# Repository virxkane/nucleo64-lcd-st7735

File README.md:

# nucleo64-lcd-st7735
LCD shield for STM32 Nucleo-64 boards.

This shield is designed for connecting to STM32 Nucleo-64 boards via Arduino<sup>TM</sup> Uno V3.

**WARNING:** Although this shield can be connected to the Arduino<sup>TM</sup> UNO, it is incompatible in logic levels, so it is strictly forbidden to connect this way, otherwise this display will fail!

### Hardware
* The GMT177-01 module is used as a display and is compatible in size and pins. The display controller used is **ST7735**. The display data bus is connected to the hardware SPI. PWM can be used  to control the brightness of the screen backlight.
* Joystick K1-1504SA-03 and one button KLS7-TS6601 can be used for control. Both are connected to 3 General Purpose I/O ports via diodes.
* EEPROM memory M24C08 can be used to store user data. This IC is connected to the I2C hardware bus.
* Two LEDs are connected to ports A0(PA0) and A1(PA1).
* A separate button IT-1187-160GM-G is provided to reset the controller.

### Demo firmware
Two versions of the demo firmware have been written to work on the NUCLEO-F446RE and this shield, one using CMSIS, the other using HAL. Both are under BSD-3-Clause License.
* Using CMSIS: [nucleo-f446re-st7735spi-shield](https://github.com/virxkane/nucleo-f446re-st7735spi-shield)
* Using HAL: [nucleo-f446re-st7735spi-shield-hal](https://github.com/virxkane/nucleo-f446re-st7735spi-shield-hal)

#### Compare performance
| # |  bpp variant  | fill period, ms | transfer period, CMSIS, ms | transfer period, HAL, ms |
|---|---------------|--------|-----------|---------|
| 1 | fb=1, lcd=12  |     3  |      23   |    40   |
| 2 | fb=1, lcd=16  |     3  |      30   |    60   |
| 3 | fb=1, lcd=18  |     3  |      44   |    74   |
| 4 | fb=4, lcd=12  |     3  |      23   |    39   |
| 5 | fb=4, lcd=16  |     3  |      30   |    58   |
| 6 | fb=4, lcd=18  |     3  |      44   |    73   |
| 7 | fb=8, lcd=12  |     2  |      23   |    39   |
| 8 | fb=8, lcd=16  |     2  |      30   |    59   |
| 9 | fb=8, lcd=18  |     2  |      44   |    73   |
| 10 | fb=16, lcd=12 |    3  |      22   |    39   |
| 11 | fb=16, lcd=16 |    3  |      30   |    59   |
| 12 | fb=16, lcd=18 |    3  |      44   |    75   |
| 13 | fb=24, lcd=12 |    3  |      22   |    38   |
| 14 | fb=24, lcd=16 |    3  |      30   |    61   |
| 15 | fb=24, lcd=18 |    3  |      44   |    73   |

Where *fb* - frame buffer color depth, *lcd* - LCD module color depth, *fill period* - frame buffer fill period, *transfer period* - period of frame buffer transmission to LCD module.

Tests performed at SPI clock 11,25 Mbits/s.

### Schematic

### Some photo
Unfortunately, there are currently no rev.4 boards, and the existing rev.3 boards have a small error - the LEDs are connected to RX/D0(PA3) and TX/D1(PA2), which by default are connected to the USART of the on-board ST-LINK/V2-1 programmer. To correct this drawback, two wire are placed on the bottom of the board to ports A0(PA0) and A1(PA1). The boards of the rev.4 are free from this drawback.

#### Front view (rev.3)

#### Back view (rev.3)

#### Paired with NUCLEO-F446RE with running [demo](https://github.com/virxkane/nucleo-f446re-st7735spi-shield) (rev.3)

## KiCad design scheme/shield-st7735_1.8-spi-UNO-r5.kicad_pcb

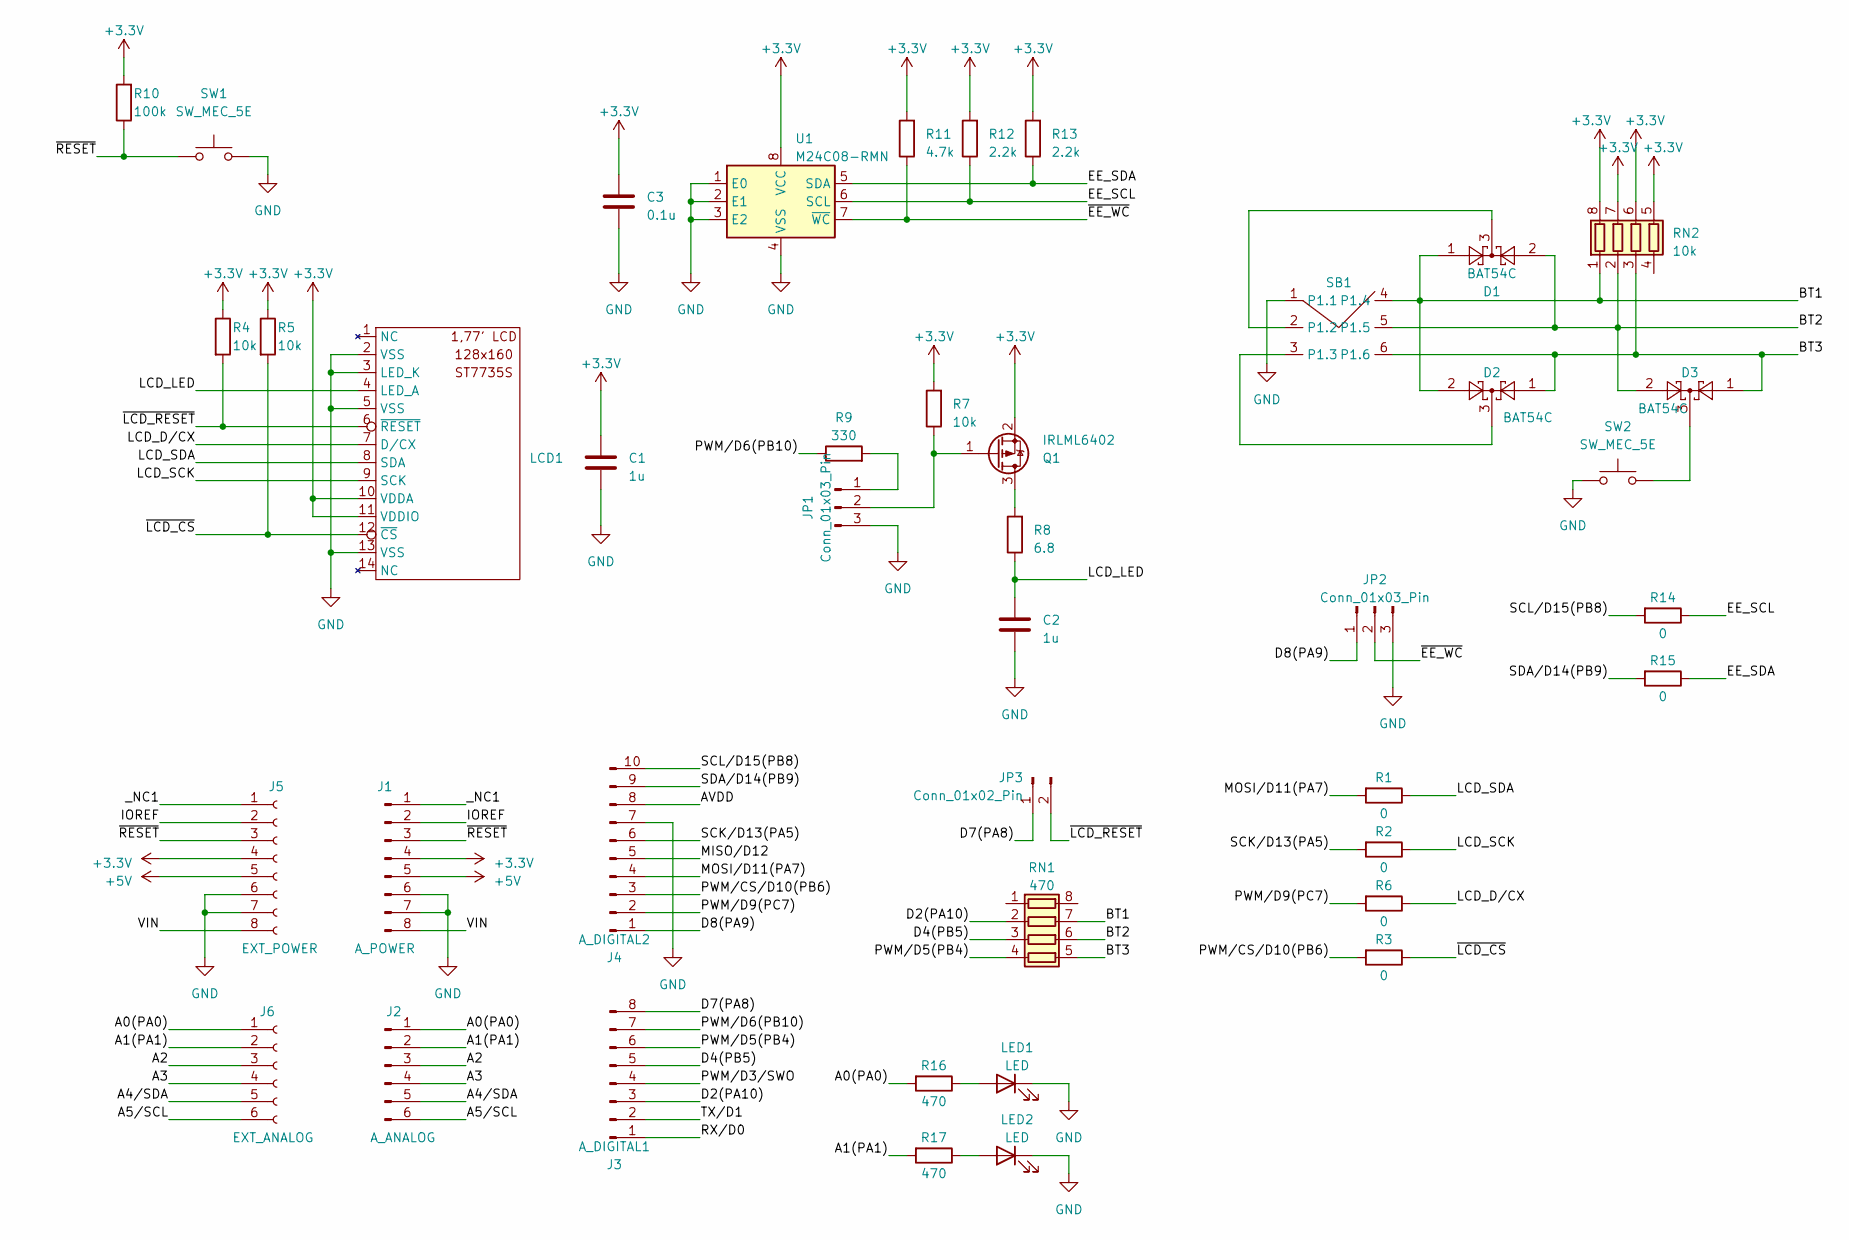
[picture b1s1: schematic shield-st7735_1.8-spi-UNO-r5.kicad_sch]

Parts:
C1, C2: 1u; C_1206_3216Metric
C3: 0.1u; C_1206_3216Metric
D1, D2, D3: BAT54C; SOT-23
J1: A_POWER; PinHeader_1x08_P2.54mm_Vertical
J2: A_ANALOG; PinHeader_1x06_P2.54mm_Vertical
J3: A_DIGITAL1; PinHeader_1x08_P2.54mm_Vertical
J4: A_DIGITAL2; PinHeader_1x10_P2.54mm_Vertical
J5: EXT_POWER; PinSocket_1x08_P2.54mm_Vertical
J6: EXT_ANALOG; PinSocket_1x06_P2.54mm_Vertical
JP1, JP2: Conn_01x03_Pin; PinHeader_1x03_P2.54mm_Vertical
JP3: Conn_01x02_Pin; PinHeader_1x02_P2.54mm_Vertical
LCD1: GMT177-01
LED1, LED2: LED; LED_0805_2012Metric
Q1: IRLML6402; SOT-23
R1, R2, R3, R6, R14, R15: 0; R_1206_3216Metric
R4, R5, R7: 10k; R_1206_3216Metric
R8: 6.8; R_1206_3216Metric
R9: 330; R_1206_3216Metric
R10: 100k; R_1206_3216Metric
R11: 4.7k; R_1206_3216Metric
R12, R13: 2.2k; R_1206_3216Metric
R16, R17: 470; R_1206_3216Metric
RN1: 470; R_Array_Convex_4x0603
RN2: 10k; R_Array_Convex_4x0603
SB1: K1-1504SA-03
SW1: SW_MEC_5E; SW_SPST_SKQG_WithStem
SW2: SW_MEC_5E; SW_PUSH_6mm_H4.3mm
U1: M24C08-RMN; SOIC-8_3.9x4.9mm_P1.27mm

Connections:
+3.3V: C1.1, C3.1, J1.4, J5.4, LCD1.10 (VDDA), LCD1.11 (VDDIO), Q1.2 (S), R4.1, R5.1, R7.2, R10.2, R11.2, R12.2, R13.2, RN2.5 (R4.2), RN2.6 (R3.2), RN2.7 (R2.2), RN2.8 (R1.2), U1.8 (VCC)
+5V: J1.5, J5.5
/A0(PA0): J2.1, J6.1, R16.2
/A1(PA1): J2.2, J6.2, R17.2
/A2: J2.3, J6.3
/A3: J2.4, J6.4
/A4/SDA: J2.5, J6.5
/A5/SCL: J2.6, J6.6
/AVDD: J4.8
/BT1: D1.1, D2.2, RN1.7 (R2.2), RN2.1 (R1.1), SB1.4 (P1.4)
/BT2: D1.2, D3.2, RN1.6 (R3.2), RN2.2 (R2.1), SB1.5 (P1.5)
/BT3: D2.1, D3.1, RN1.5 (R4.2), RN2.3 (R3.1), SB1.6 (P1.6)
/D2(PA10): J3.3, RN1.2 (R2.1)
/D4(PB5): J3.5, RN1.3 (R3.1)
/D7(PA8): J3.8, JP3.1
/D8(PA9): J4.1, JP2.1
/EE_SCL: R12.1, R14.1, U1.6 (SCL)
/EE_SDA: R13.1, R15.1, U1.5 (SDA)
/IOREF: J1.2, J5.2
/LCD_D/CX: LCD1.7 (D/CX), R6.1
/LCD_LED: C2.1, LCD1.4 (LED_A), R8.1
/LCD_SCK: LCD1.9 (SCK), R2.1
/LCD_SDA: LCD1.8 (SDA), R1.1
/MISO/D12: J4.5
/MOSI/D11(PA7): J4.4, R1.2
/PWM/CS/D10(PB6): J4.3, R3.2
/PWM/D3/SWO: J3.4
/PWM/D5(PB4): J3.6, RN1.4 (R4.1)
/PWM/D6(PB10): J3.7, R9.1
/PWM/D9(PC7): J4.2, R6.2
/RX/D0: J3.1
/SCK/D13(PA5): J4.6, R2.2
/SCL/D15(PB8): J4.10, R14.2
/SDA/D14(PB9): J4.9, R15.2
/TX/D1: J3.2
/VIN: J1.8, J5.8
/_NC1: J1.1, J5.1
/~EE_WC: JP2.2, R11.1, U1.7 (~WC)
/~LCD_CS: LCD1.12 (~CS), R3.1, R5.2
/~LCD_RESET: JP3.2, LCD1.6 (~RESET), R4.2
/~RESET: J1.3, J5.3, R10.1, SW1.1
GND: C1.2, C2.2, C3.2, J1.6, J1.7, J4.7, J5.6, J5.7, JP1.3, JP2.3, LCD1.2 (VSS), LCD1.3 (LED_K), LCD1.5 (VSS), LCD1.13 (VSS), LED1.1 (K), LED2.1 (K), SB1.1 (P1.1), SW1.2, SW2.1, U1.1 (E0), U1.2 (E1), U1.3 (E2), U1.4 (VSS)
unnamed: D3.3, SW2.2
unnamed: JP1.1, R9.2
unnamed: JP1.2, Q1.1 (G), R7.1
unnamed: LED1.2 (A), R16.1
unnamed: LED2.2 (A), R17.1
unnamed: Q1.3 (D), R8.2
unnamed: D1.3, SB1.2 (P1.2)
unnamed: D2.3, SB1.3 (P1.3)

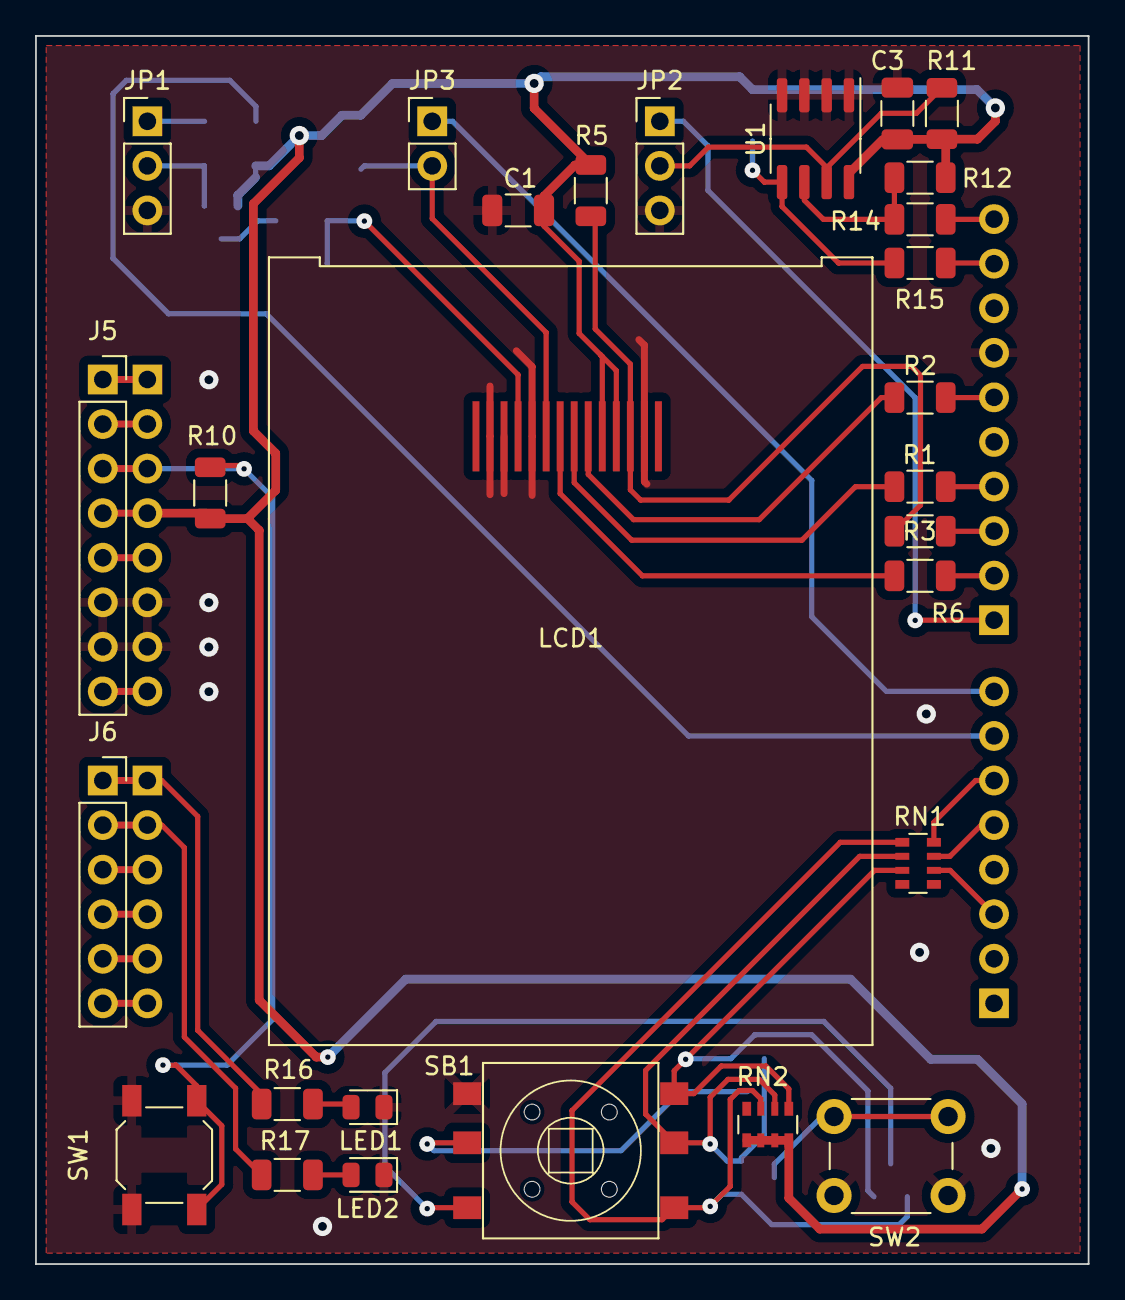
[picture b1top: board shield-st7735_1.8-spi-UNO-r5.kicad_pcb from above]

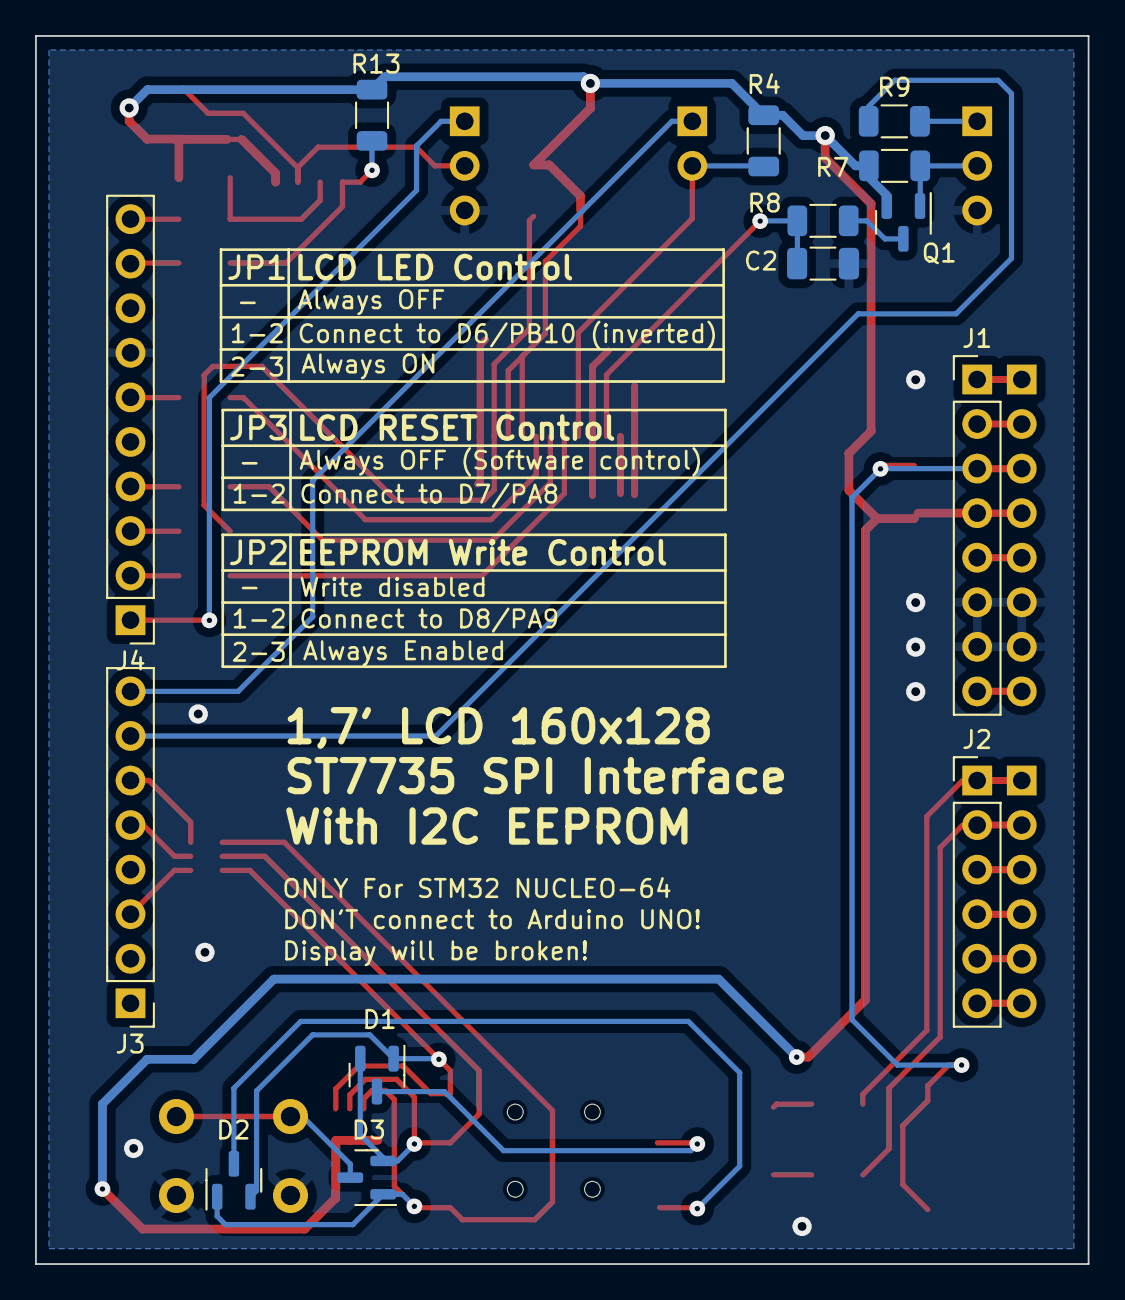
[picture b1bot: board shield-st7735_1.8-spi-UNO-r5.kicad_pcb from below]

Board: 2 copper layers, 60.0 x 70.0 mm, 42 parts (14 on the bottom side), 45 nets.

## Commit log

2021-11-02 Add schematic.
2021-11-02 Added schematic in image format.
2021-11-02 Added photo for patched rev.3
2023-09-10 New revision, the project has been remade in KiCAD.
